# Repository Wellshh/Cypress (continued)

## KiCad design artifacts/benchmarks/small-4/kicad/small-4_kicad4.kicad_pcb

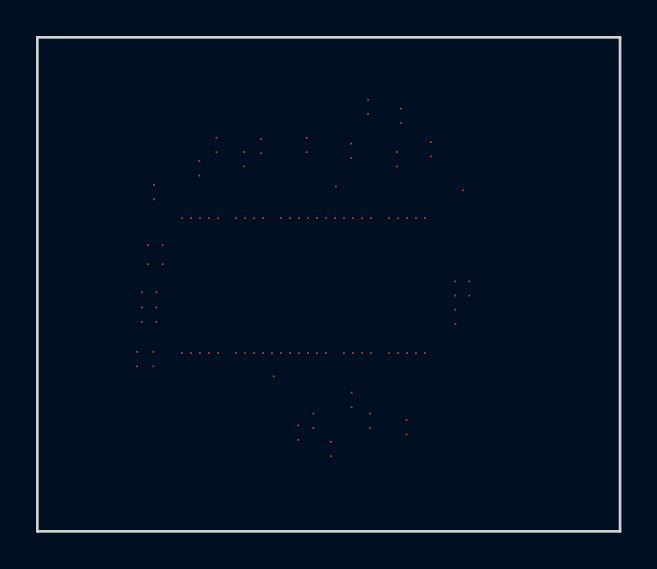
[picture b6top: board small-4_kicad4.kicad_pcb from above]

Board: 2 copper layers, 32.4 x 27.4 mm, 43 parts (0 on the bottom side), 39 nets, no tracks yet.

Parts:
C0: C0; 195-0128-000
C1: C1; 195-0128-000
C2: C2; 195-3953-000
C3: C3; 195-3953-000
C4: C4; 195-3953-000
C5: C5; 195-3953-000
C6: C6; 195-3953-000
C7: C7; 195-0003-000
C8: C8; 195-0128-000
C9: C9; 195-0128-000
C10: C10; 195-0128-000
C11: C11; 195-0128-000
C12: C12; 195-0128-000
C13: C13; 195-0128-000
C14: C14; 195-0128-000
C15: C15; 195-0128-000
C16: C16; 195-3953-000
C17: C17; 195-0128-000
C18: C18; 195-0128-000
C19: C19; 195-0128-000
C20: C20; 195-0128-000
C21: C21; 195-0128-000
C22: C22; 195-0128-000
C23: C23; 195-0128-000
C24: C24; 195-0128-000
C25: C25; 195-0128-000
C26: C26; 195-0128-000
C27: C27; 195-0128-000
C28: C28; 195-0128-000
C29: C29; 195-0128-000
C30: C30; 195-0128-000
C31: C31; 195-0128-000
C32: C32; 195-0128-000
C33: C33; 195-0128-000
C34: C34; 195-0128-000
C35: C35; 195-0128-000
C36: C36; 195-2655-000
C37: C37; 195-2655-000
C38: C38; 195-0128-000
C39: C39; 032-0863-000
C40: C40; 032-0863-000
C41: C41; 195-3953-000
C42: C42; 115-3050-000

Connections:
NET_49: C3.1, C6.1, C7.1, C39.1, C40.1, C41.1, C42.18, C42.46
NET_153: C6.2, C42.27
NET_156: C4.1, C42.28
NET_158: C5.1, C42.29
NET_368: C17.1, C42.35
NET_389: C18.1, C42.33
NET_548: C1.1, C42.31
NET_550: C2.1, C36.2, C42.30
NET_552: C7.2, C37.2, C42.56
NET_563: C14.1, C42.42
NET_572: C0.1, C42.43
NET_574: C9.1, C42.44
NET_894: C12.1, C42.54
NET_912: C15.1, C42.38
NET_915: C34.1, C42.40
NET_917: C35.1, C42.37
NET_919: C33.1, C42.41
NET_921: C16.1, C42.36
NET_929: C30.1, C42.24
NET_2211: C3.2, C42.2
NET_2212: C41.2, C42.1
NET_2373: C8.1, C42.32
NET_2488: C31.1, C42.25
NET_3928: C24.1, C42.15
NET_3941: C10.1, C42.20
NET_3945: C38.1, C42.9
NET_3983: C23.1, C42.16
NET_3999: C25.1, C42.10
NET_4018: C19.1, C42.48
NET_4022: C20.1, C42.22
NET_4025: C11.1, C42.45
NET_4035: C13.1, C42.21
NET_4043: C27.1, C42.7
NET_4053: C26.1, C42.8
NET_4079: C32.1, C42.4
NET_4091: C28.1, C42.5
NET_4189: C21.1, C42.19
NET_4191: C22.1, C42.17
NET_4249: C29.1, C42.3

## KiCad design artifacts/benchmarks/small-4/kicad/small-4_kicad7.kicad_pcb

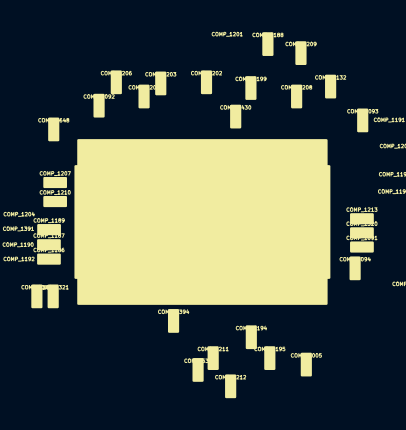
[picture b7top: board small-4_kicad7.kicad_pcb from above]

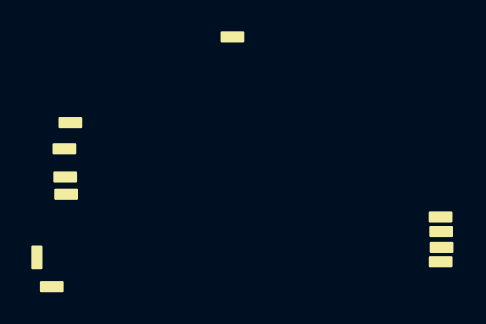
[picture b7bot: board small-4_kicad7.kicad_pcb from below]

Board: 2 copper layers, 43 parts (11 on the bottom side), 39 nets, no tracks yet.

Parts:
COMP_534: COMP_534; 195-0128-000
COMP_1005: COMP_1005; 195-0128-000
COMP_1091: COMP_1091; 195-3953-000
COMP_1092: COMP_1092; 195-3953-000
COMP_1093: COMP_1093; 195-3953-000
COMP_1094: COMP_1094; 195-3953-000
COMP_1132: COMP_1132; 195-3953-000
COMP_1181: COMP_1181; 195-0003-000
COMP_1186: COMP_1186; 195-0128-000
COMP_1187: COMP_1187; 195-0128-000
COMP_1188: COMP_1188; 195-0128-000
COMP_1189: COMP_1189; 195-0128-000
COMP_1190: COMP_1190; 195-0128-000
COMP_1191: COMP_1191; 195-0128-000
COMP_1192: COMP_1192; 195-0128-000
COMP_1193: COMP_1193; 195-0128-000
COMP_1194: COMP_1194; 195-3953-000
COMP_1195: COMP_1195; 195-0128-000
COMP_1196: COMP_1196; 195-0128-000
COMP_1197: COMP_1197; 195-0128-000
COMP_1198: COMP_1198; 195-0128-000
COMP_1199: COMP_1199; 195-0128-000
COMP_1200: COMP_1200; 195-0128-000
COMP_1201: COMP_1201; 195-0128-000
COMP_1202: COMP_1202; 195-0128-000
COMP_1203: COMP_1203; 195-0128-000
COMP_1204: COMP_1204; 195-0128-000
COMP_1205: COMP_1205; 195-0128-000
COMP_1206: COMP_1206; 195-0128-000
COMP_1207: COMP_1207; 195-0128-000
COMP_1208: COMP_1208; 195-0128-000
COMP_1209: COMP_1209; 195-0128-000
COMP_1210: COMP_1210; 195-0128-000
COMP_1211: COMP_1211; 195-0128-000
COMP_1212: COMP_1212; 195-0128-000
COMP_1213: COMP_1213; 195-0128-000
COMP_1320: COMP_1320; 195-2655-000
COMP_1321: COMP_1321; 195-2655-000
COMP_1391: COMP_1391; 195-0128-000
COMP_1394: COMP_1394; 032-0863-000
COMP_1430: COMP_1430; 032-0863-000
COMP_1648: COMP_1648; 195-3953-000
COMP_2862: COMP_2862; 115-3050-000

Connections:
NET_49: COMP_1092.1, COMP_1132.1, COMP_1181.1, COMP_1394.1, COMP_1430.1, COMP_1648.1, COMP_2862.18, COMP_2862.46
NET_153: COMP_1132.2, COMP_2862.27
NET_156: COMP_1093.1, COMP_2862.28
NET_158: COMP_1094.1, COMP_2862.29
NET_368: COMP_1195.1, COMP_2862.35
NET_389: COMP_1196.1, COMP_2862.33
NET_548: COMP_1005.1, COMP_2862.31
NET_550: COMP_1091.1, COMP_1320.2, COMP_2862.30
NET_552: COMP_1181.2, COMP_1321.2, COMP_2862.56
NET_563: COMP_1192.1, COMP_2862.42
NET_572: COMP_534.1, COMP_2862.43
NET_574: COMP_1187.1, COMP_2862.44
NET_894: COMP_1190.1, COMP_2862.54
NET_912: COMP_1193.1, COMP_2862.38
NET_915: COMP_1212.1, COMP_2862.40
NET_917: COMP_1213.1, COMP_2862.37
NET_919: COMP_1211.1, COMP_2862.41
NET_921: COMP_1194.1, COMP_2862.36
NET_929: COMP_1208.1, COMP_2862.24
NET_2211: COMP_1092.2, COMP_2862.2
NET_2212: COMP_1648.2, COMP_2862.1
NET_2373: COMP_1186.1, COMP_2862.32
NET_2488: COMP_1209.1, COMP_2862.25
NET_3928: COMP_1202.1, COMP_2862.15
NET_3941: COMP_1188.1, COMP_2862.20
NET_3945: COMP_1391.1, COMP_2862.9
NET_3983: COMP_1201.1, COMP_2862.16
NET_3999: COMP_1203.1, COMP_2862.10
NET_4018: COMP_1197.1, COMP_2862.48
NET_4022: COMP_1198.1, COMP_2862.22
NET_4025: COMP_1189.1, COMP_2862.45
NET_4035: COMP_1191.1, COMP_2862.21
NET_4043: COMP_1205.1, COMP_2862.7
NET_4053: COMP_1204.1, COMP_2862.8
NET_4079: COMP_1210.1, COMP_2862.4
NET_4091: COMP_1206.1, COMP_2862.5
NET_4189: COMP_1199.1, COMP_2862.19
NET_4191: COMP_1200.1, COMP_2862.17
NET_4249: COMP_1207.1, COMP_2862.3

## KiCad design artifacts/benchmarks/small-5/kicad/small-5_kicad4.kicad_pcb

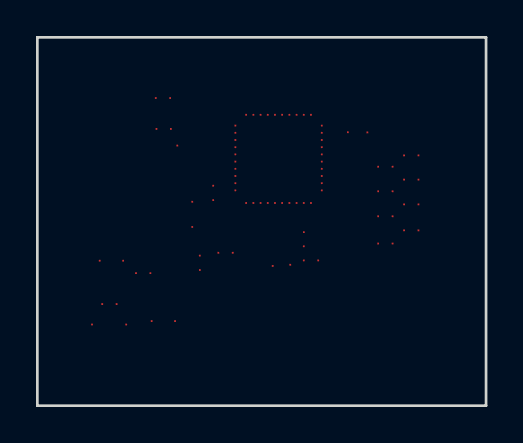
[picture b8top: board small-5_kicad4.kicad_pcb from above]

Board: 2 copper layers, 24.9 x 20.5 mm, 41 parts (0 on the bottom side), 29 nets, no tracks yet.

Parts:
C0: C0; 195-0385-000
C1: C1; 195-0313-000
C2: C2; 195-3953-000
C3: C3; 195-3953-000
C4: C4; 195-3953-000
C5: C5; 195-3953-000
C6: C6; 195-0234-000
C7: C7; 195-0234-000
C8: C8; 195-0234-000
C9: C9; 195-0234-000
C10: C10; 195-0234-000
C11: C11; 195-0234-000
C12: C12; 195-0234-000
C13: C13; 195-0234-000
C14: C14; 195-0234-000
C15: C15; 195-0234-000
C16: C16; 195-0149-000
C17: C17; 195-0148-000
C18: C18; 195-3907-000
C19: C19; 195-0003-000
C20: C20; 195-0090-000
C21: C21; 195-0254-000
C22: C22; 195-0055-000
C23: C23; 195-0004-000
C24: C24; 195-2655-000
C25: C25; 195-2655-000
C26: C26; 032-0783-000
C27: C27; 032-0783-000
C28: C28; 036-0022-000
C29: C29; 036-0022-000
C30: C30; 032-1567-000
C31: C31; 032-1567-000
C32: C32; 035-0012-000
C33: C33; 032-0863-000
C34: C34; 032-0863-000
C35: C35; 032-0253-000
C36: C36; 195-1765-000
C37: C37; 195-1765-000
C38: C38; 195-1765-000
C39: C39; 316-0923-000
C40: C40; 315-0964-000

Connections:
NET_54: C4.1, C5.1, C18.2, C34.1, C35.1, C39.12
NET_537: C5.2, C39.1
NET_538: C3.2, C39.37
NET_945: C6.1, C7.1, C8.1, C9.1, C10.1, C11.1, C12.1, C13.1, C14.1, C15.1, C39.21
NET_946: C0.1, C39.26
NET_947: C24.2, C30.1, C40.1
NET_948: C17.1, C39.28
NET_949: C17.2, C39.29
NET_951: C22.2, C25.1
NET_4009: C1.1, C21.2, C39.24
NET_4226: C23.1, C31.1, C36.2, C39.40
NET_4229: C15.2, C39.27
NET_4231: C6.2, C39.20
NET_4233: C7.2, C39.19
NET_4235: C8.2, C39.18
NET_4237: C9.2, C39.17
NET_4239: C10.2, C39.16
NET_4241: C11.2, C39.15
NET_4243: C12.2, C39.14
NET_4245: C13.2, C39.13
NET_4247: C14.2, C39.30
NET_4248: C2.1, C39.36
NET_4250: C4.2, C39.38
NET_4252: C32.2, C39.32
NET_4254: C32.1, C37.1, C39.31
NET_4255: C22.1, C29.1, C39.25
NET_4280: C19.1, C20.2, C28.1, C39.22
NET_4283: C16.1, C24.1, C26.1, C38.1, C40.2
NET_4286: C3.1, C21.1, C27.1, C33.1, C39.23
